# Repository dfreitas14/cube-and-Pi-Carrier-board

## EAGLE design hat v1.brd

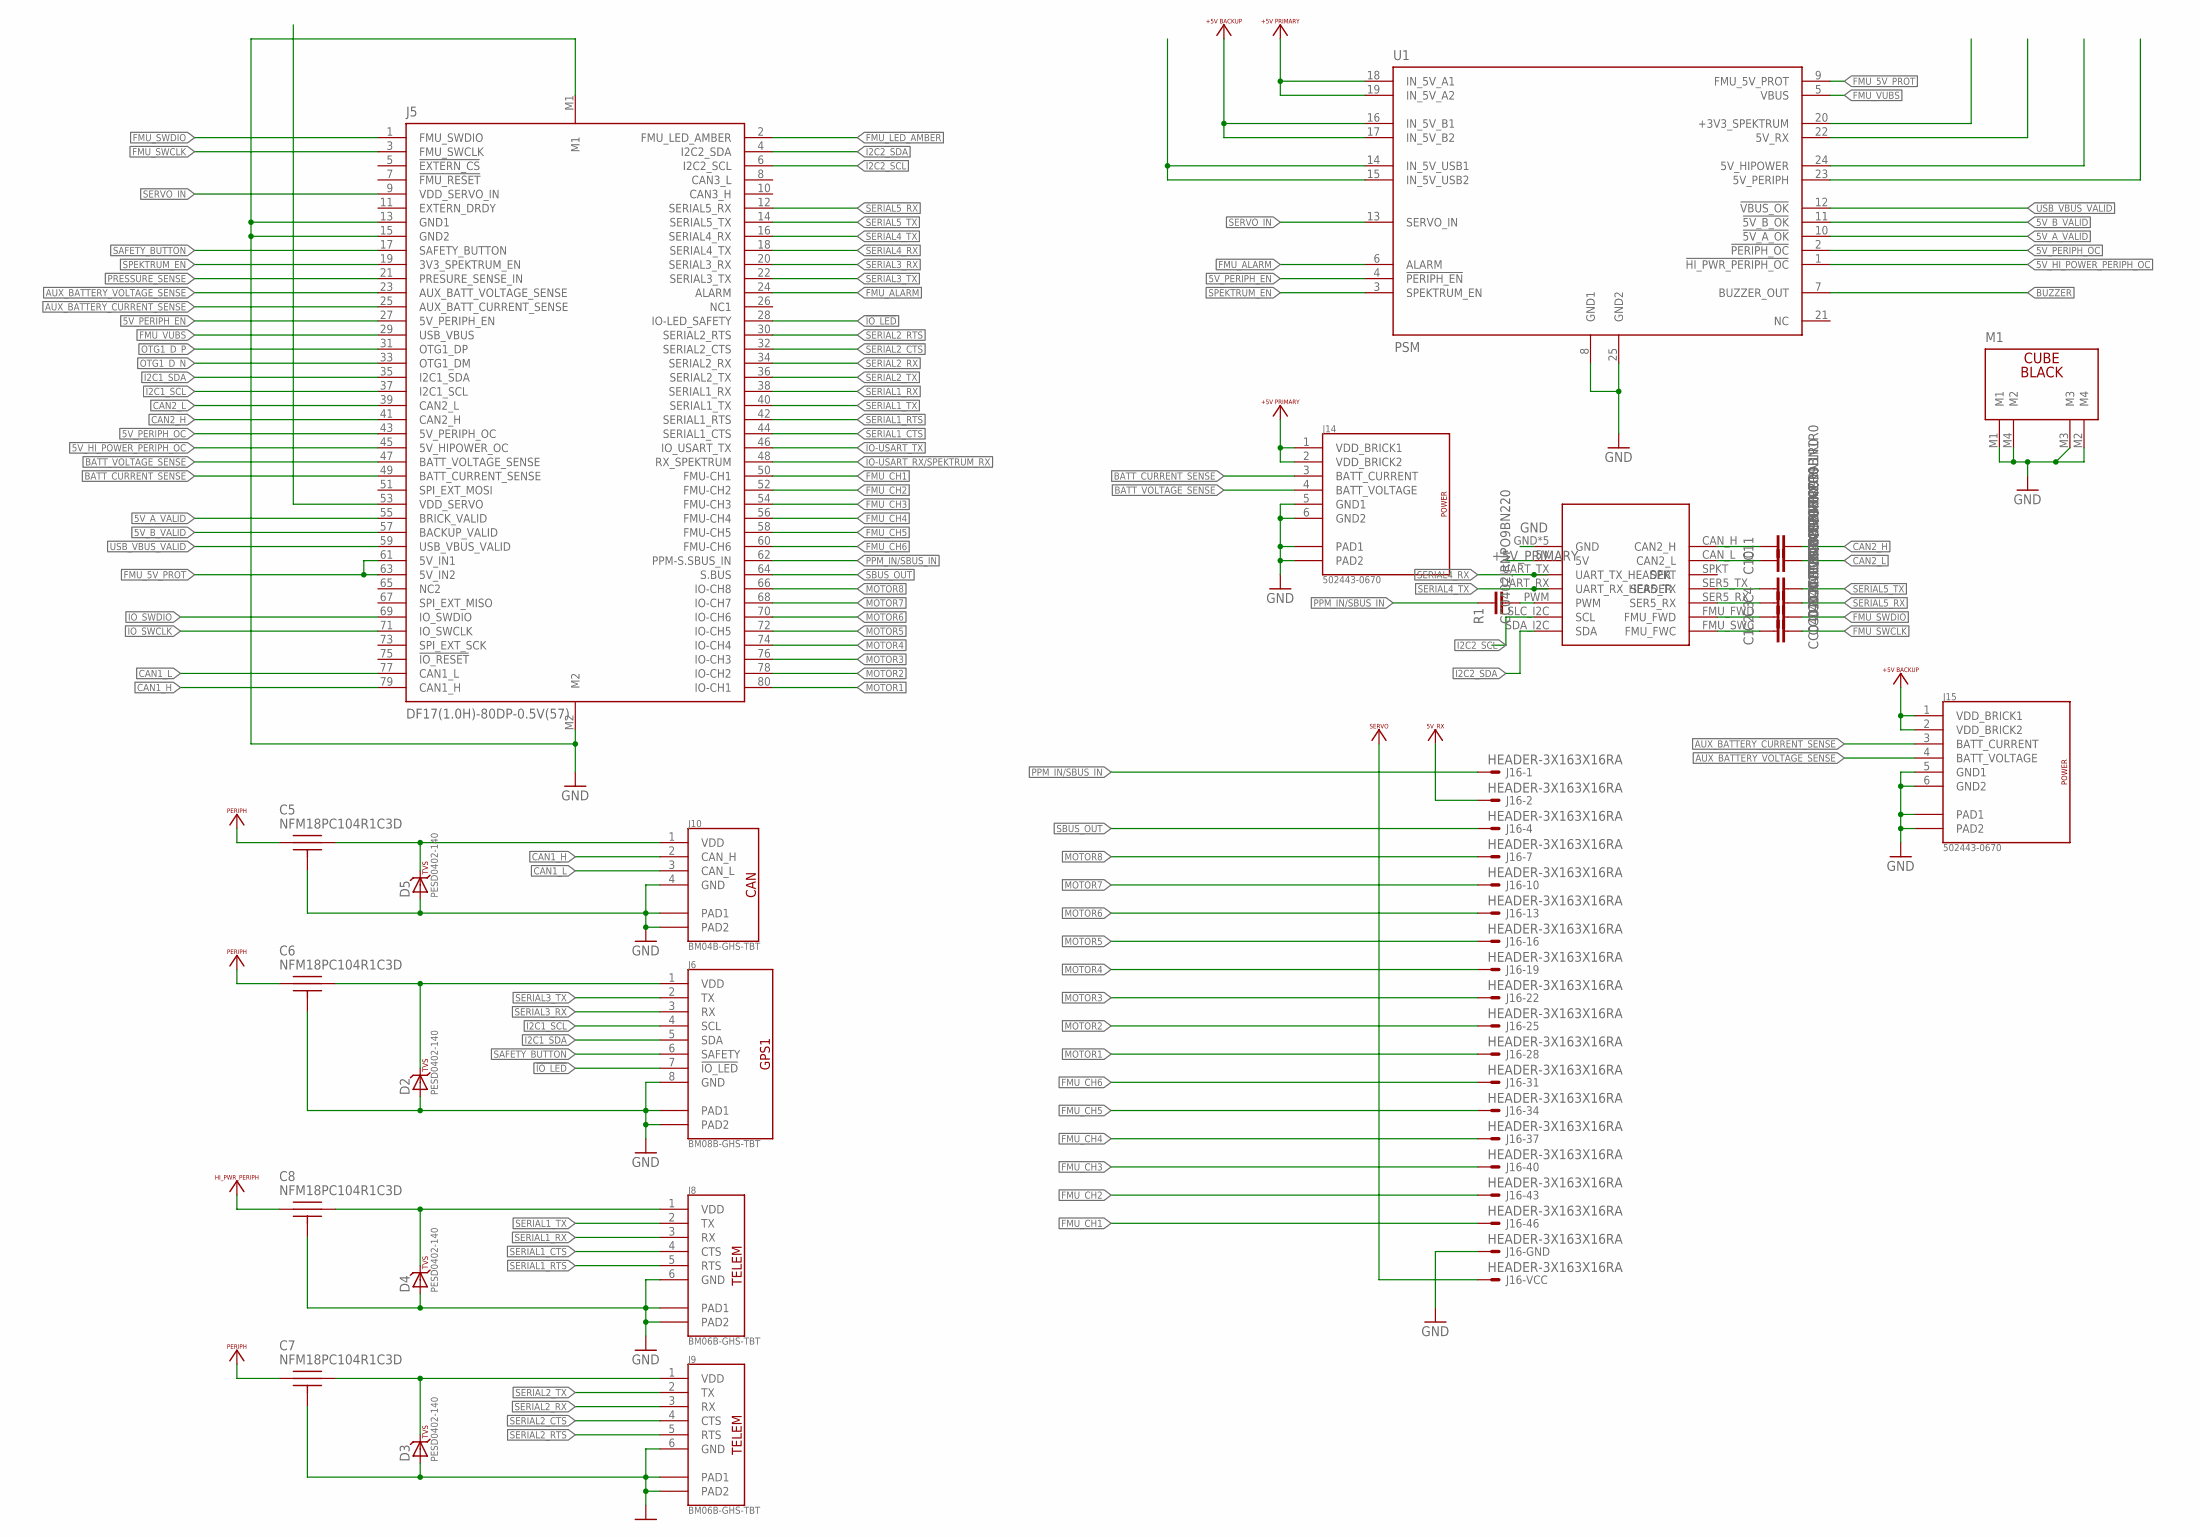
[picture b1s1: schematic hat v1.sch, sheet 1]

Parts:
C1, C2, C3, C4, C10, C11: CC0402CRNPO9BN1R0; CAP_0402
C5, C6, C7, C8: NFM18PC104R1C3D; KYOCERA-KNH16-DA
D2, D3, D4, D5: PESD0402-140; 0402-TVS
J5: DF17(1.0H)-80DP-0.5V(57)
J6: BM08B-GHS-TBT
J8, J9: BM06B-GHS-TBT
J10: BM04B-GHS-TBT
J14, J15: 502443-0670
J16: HEADER-3X163X16RA; 3X16RA
M1: CUBE_BLACK; CUBE
R1: CC0402JRNPO9BN220; CAP_0402
U1: PSM
U$1: RPI

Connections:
5V_A_VALID: J5.55 (BRICK_VALID), U1.10 (!5V_A_OK)
5V_B_VALID: J5.57 (BACKUP_VALID), U1.11 (!5V_B_OK)
5V_HI_POWER_PERIPH_OC: J5.45 (5V_HIPOWER_OC), U1.1 (!HI_PWR_PERIPH_OC)
5V_PERIPH_EN: J5.27 (5V_PERIPH_EN), U1.4 (!PERIPH_EN)
5V_PERIPH_OC: J5.43 (5V_PERIPH_OC), U1.2 (!PERIPH_OC)
!FMU_LED_AMBER: J5.2 (FMU_LED_AMBER)
!IO_LED: J5.28 (IO-LED_SAFETY), J6.7 (!IO_LED)
+3V3_SPEKTRUM: U1.20 (+3V3_SPEKTRUM)
+5V_BACKUP: J15.1 (VDD_BRICK1), J15.2 (VDD_BRICK2), U1.16 (IN_5V_B1), U1.17 (IN_5V_B2)
+5V_PRIMARY: J14.1 (VDD_BRICK1), J14.2 (VDD_BRICK2), U1.18 (IN_5V_A1), U1.19 (IN_5V_A2), U$1.5V
AUX_BATTERY_CURRENT_SENSE: J5.25 (AUX_BATT_CURRENT_SENSE), J15.3 (BATT_CURRENT)
AUX_BATTERY_VOLTAGE_SENSE: J5.23 (AUX_BATT_VOLTAGE_SENSE), J15.4 (BATT_VOLTAGE)
BATT_CURRENT_SENSE: J5.49 (BATT_CURRENT_SENSE), J14.3 (BATT_CURRENT)
BATT_VOLTAGE_SENSE: J5.47 (BATT_VOLTAGE_SENSE), J14.4 (BATT_VOLTAGE)
BUZZER: U1.7 (BUZZER_OUT)
CAN1_H: J5.79 (CAN1_H), J10.2 (CAN_H)
CAN1_L: J5.77 (CAN1_L), J10.3 (CAN_L)
CAN2_H: C11.2, J5.41 (CAN2_H)
CAN2_L: C10.2, J5.39 (CAN2_L)
FMU_5V_PROT: J5.61 (5V_IN1), J5.63 (5V_IN2), U1.9 (FMU_5V_PROT)
FMU_CH1: J5.50 (FMU-CH1), J16.46
FMU_CH2: J5.52 (FMU-CH2), J16.43
FMU_CH3: J5.54 (FMU-CH3), J16.40
FMU_CH4: J5.56 (FMU-CH4), J16.37
FMU_CH5: J5.58 (FMU-CH5), J16.34
FMU_CH6: J5.60 (FMU-CH6), J16.31
FMU_SWCLK: C1.2, J5.3 (FMU_SWCLK)
FMU_SWDIO: C2.2, J5.1 (FMU_SWDIO)
FMU_VUBS: J5.29 (USB_VBUS), U1.5 (VBUS)
GND: C5.P$3, C5.P$4, C5.P$5, C6.P$3, C6.P$4, C6.P$5, C7.P$3, C7.P$4, C7.P$5, C8.P$3, C8.P$4, C8.P$5, D2.A, D3.A, D4.A, D5.A, J5.13 (GND1), J5.15 (GND2), J5.M1, J5.M2, J6.8 (GND), J6.PAD1, J6.PAD2, J8.6 (GND), J8.PAD1, J8.PAD2, J9.6 (GND), J9.PAD1, J9.PAD2, J10.4 (GND), J10.PAD1, J10.PAD2, J14.5 (GND1), J14.6 (GND2), J14.PAD1, J14.PAD2, J15.5 (GND1), J15.6 (GND2), J15.PAD1, J15.PAD2, J16.3, J16.6, J16.9, J16.12, J16.15, J16.18, J16.21, J16.24, J16.27, J16.30, J16.33, J16.36, J16.39, J16.42, J16.45, J16.48, M1.M1, M1.M2 (M4), M1.M3, M1.M4 (M2), U1.8 (GND1), U1.25 (GND2), U$1.GND, U$1.GND1 (GND), U$1.GND2 (GND), U$1.GND3 (GND), U$1.GND4 (GND)
I2C1_SCL: J5.37 (I2C1_SCL), J6.4 (SCL)
I2C1_SDA: J5.35 (I2C1_SDA), J6.5 (SDA)
I2C2_SCL: J5.6 (I2C2_SCL), U$1.SLC_I2C (SCL)
I2C2_SDA: J5.4 (I2C2_SDA), U$1.SDA_I2C (SDA)
IO-USART_RX/SPEKTRUM_RX: J5.48 (RX_SPEKTRUM)
IO-USART_TX: J5.46 (IO_USART_TX)
IO_SWCLK: J5.71 (IO_SWCLK)
IO_SWDIO: J5.69 (IO_SWDIO)
MOTOR1: J5.80 (IO-CH1), J16.28
MOTOR2: J5.78 (IO-CH2), J16.25
MOTOR3: J5.76 (IO-CH3), J16.22
MOTOR4: J5.74 (IO-CH4), J16.19
MOTOR5: J5.72 (IO-CH5), J16.16
MOTOR6: J5.70 (IO-CH6), J16.13
MOTOR7: J5.68 (IO-CH7), J16.10
MOTOR8: J5.66 (IO-CH8), J16.7
unnamed: C1.1, U$1.FMU_SWC (FMU_FWC)
unnamed: C6.P$2, D2.C, J6.1 (VDD)
unnamed: C7.P$2, D3.C, J9.1 (VDD)
unnamed: C8.P$2, D4.C, J8.1 (VDD)
unnamed: C5.P$2, D5.C, J10.1 (VDD)
unnamed: C2.1, U$1.FMU_FWD
unnamed: C3.1, U$1.SER5_RX
unnamed: R1.2, U$1.PWM
unnamed: C4.1, U$1.SER5_TX
unnamed: C10.1, U$1.CAN_L (CAN2_L)
unnamed: C11.1, U$1.CAN_H (CAN2_H)
OTG1_D_N: J5.33 (OTG1_DM)
OTG1_D_P: J5.31 (OTG1_DP)
PPM_IN/SBUS_IN: J5.62 (PPM-S.SBUS_IN), J16.1, R1.1
PRESSURE_SENSE: J5.21 (PRESURE_SENSE_IN)
SAFETY_BUTTON: J5.17 (SAFETY_BUTTON), J6.6 (SAFETY)
SBUS_OUT: J5.64 (S.BUS), J16.4
SERIAL1_CTS: J5.44 (SERIAL1_CTS), J8.4 (CTS)
SERIAL1_RTS: J5.42 (SERIAL1_RTS), J8.5 (RTS)
SERIAL1_RX: J5.38 (SERIAL1_RX), J8.3 (RX)
SERIAL1_TX: J5.40 (SERIAL1_TX), J8.2 (TX)
SERIAL2_CTS: J5.32 (SERIAL2_CTS), J9.4 (CTS)
SERIAL2_RTS: J5.30 (SERIAL2_RTS), J9.5 (RTS)
SERIAL2_RX: J5.34 (SERIAL2_RX), J9.3 (RX)
SERIAL2_TX: J5.36 (SERIAL2_TX), J9.2 (TX)
SERIAL3_RX: J5.20 (SERIAL3_RX), J6.3 (RX)
SERIAL3_TX: J5.22 (SERIAL3_TX), J6.2 (TX)
SERIAL4_RX: J5.18 (SERIAL4_TX), U$1.UART_RX (UART_RX_HEADER)
SERIAL4_TX: J5.16 (SERIAL4_RX), U$1.UART_TX (UART_TX_HEADER)
SERIAL5_RX: C3.2, J5.12 (SERIAL5_RX)
SERIAL5_TX: C4.2, J5.14 (SERIAL5_TX)
SERVO_IN: J5.9 (VDD_SERVO_IN), U1.13 (SERVO_IN)
SPEKTRUM_EN: J5.19 (3V3_SPEKTRUM_EN), U1.3 (SPEKTRUM_EN)
USB_VBUS_VALID: J5.59 (USB_VBUS_VALID), U1.12 (!VBUS_OK)
VBUS: U1.14 (IN_5V_USB1), U1.15 (IN_5V_USB2)
VCCIO: J16.2, U1.22 (5V_RX)
VDD_HI_PWR_PERIPH: C8.P$1, U1.24 (5V_HIPOWER)
VDD_PERIPH: C5.P$1, C6.P$1, C7.P$1, U1.23 (5V_PERIPH)
VSERVO: J5.53 (VDD_SERVO), J16.5, J16.8, J16.11, J16.14, J16.17, J16.20, J16.23, J16.26, J16.29, J16.32, J16.35, J16.38, J16.41, J16.44, J16.47

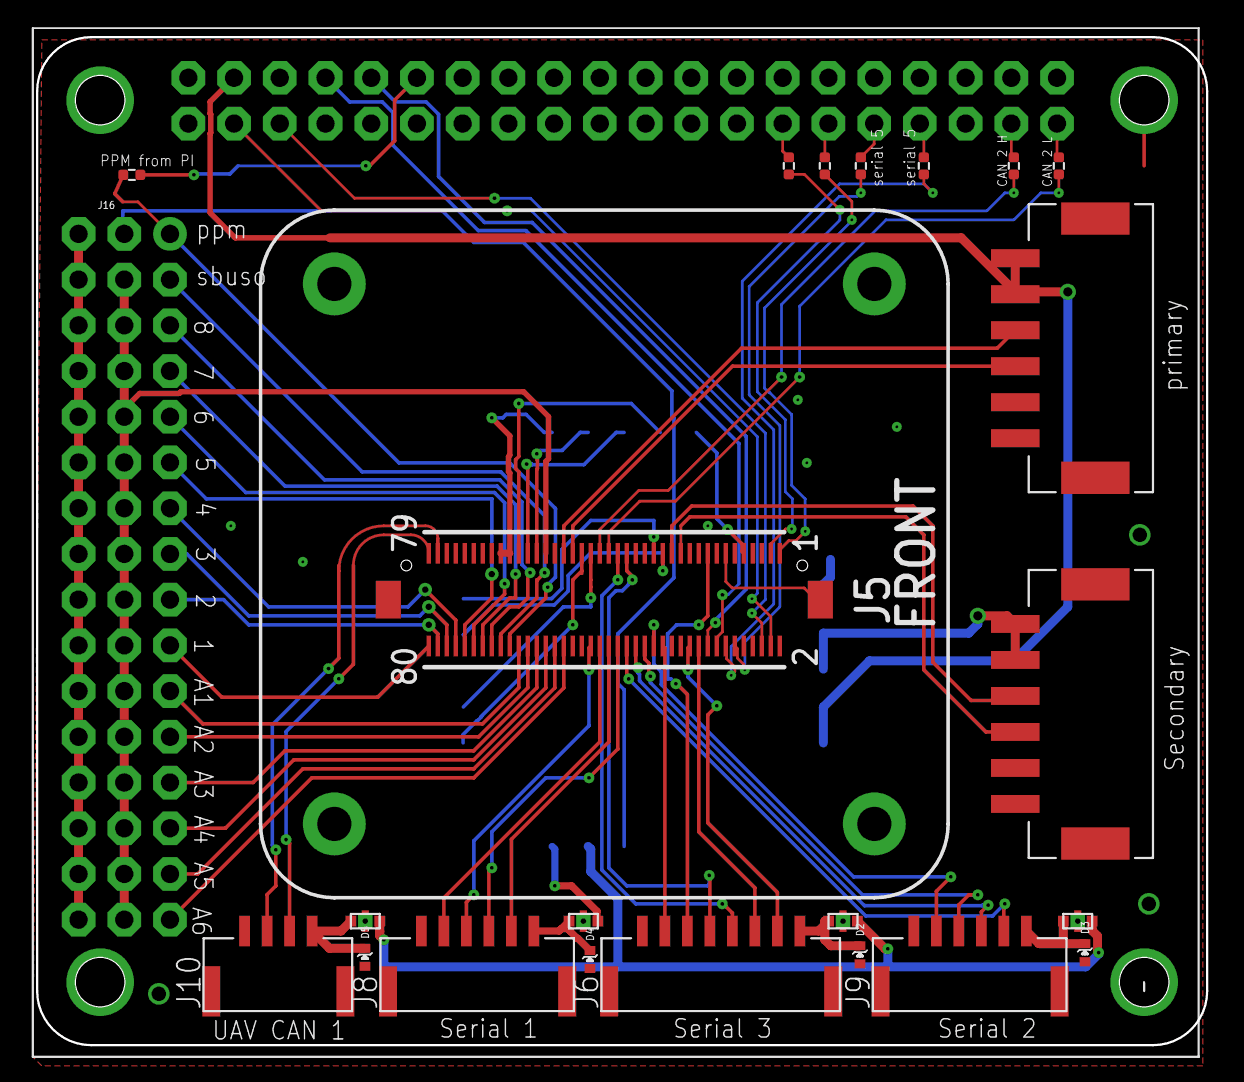
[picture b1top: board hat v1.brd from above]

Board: 2 copper layers, 65.0 x 56.0 mm, 26 parts (1 on the bottom side), 75 nets.
